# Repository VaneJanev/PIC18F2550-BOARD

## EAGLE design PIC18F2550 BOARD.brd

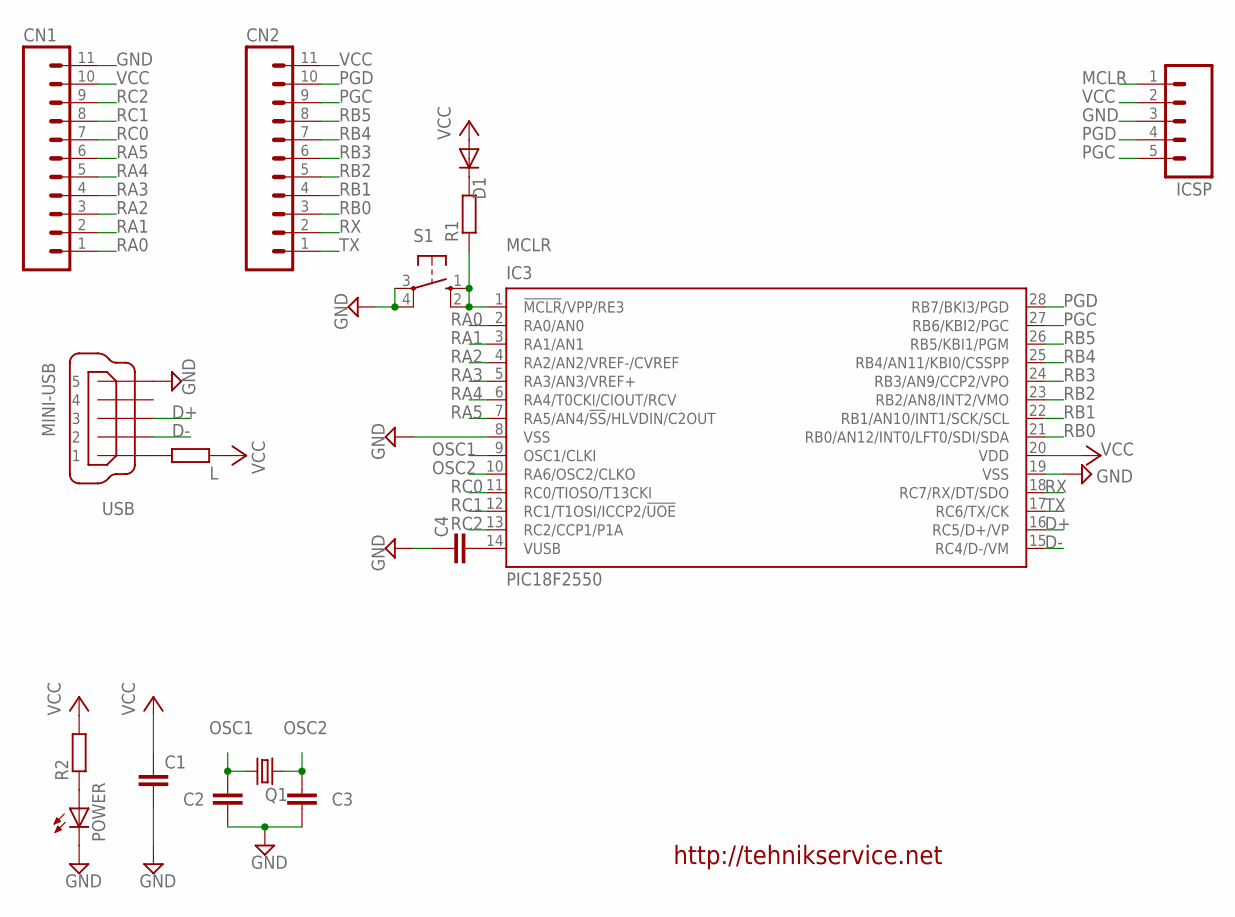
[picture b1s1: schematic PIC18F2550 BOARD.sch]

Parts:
C1, C2, C3, C4: C-EUC0402; C0402
CN1, CN2: M11; 11P
D1: DIODE-DO214AC; DO214AC
IC3: PIC18F2550; SO28W
ICSP: M05; 05P
L: R-EU_R0402; R0402
POWER: LEDCHIP-LED0805; CHIP-LED0805
Q1: CRYSTALHC49S; HC49/S
R1, R2: R-EU_R0402; R0402
S1: 10-XX; B3F-10XX
USB: MINI-USB; 32005-201

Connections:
D+: IC3.16 (RC5/D+/VP), USB.3
D-: IC3.15 (RC4/D-/VM), USB.2
GND: C1.2, C2.2, C3.2, C4.1, CN1.11, IC3.8 (VSS), IC3.19 (VSS), ICSP.3, POWER.C, S1.3, S1.4 (P1), USB.5
MCLR: IC3.1 (!MCLR!/VPP/RE3), ICSP.1, R1.1, S1.1 (S), S1.2 (S1)
unnamed: D1.C, R1.2
unnamed: POWER.A, R2.1
unnamed: C4.2, IC3.14 (VUSB)
unnamed: L.2, USB.1
OSC1: C2.1, IC3.9 (OSC1/CLKI), Q1.1
OSC2: C3.1, IC3.10 (RA6/OSC2/CLKO), Q1.2
PGC: CN2.9, IC3.27 (RB6/KBI2/PGC), ICSP.5
PGD: CN2.10, IC3.28 (RB7/BKI3/PGD), ICSP.4
RA0: CN1.1, IC3.2 (RA0/AN0)
RA1: CN1.2, IC3.3 (RA1/AN1)
RA2: CN1.3, IC3.4 (RA2/AN2/VREF-/CVREF)
RA3: CN1.4, IC3.5 (RA3/AN3/VREF+)
RA4: CN1.5, IC3.6 (RA4/T0CKI/CIOUT/RCV)
RA5: CN1.6, IC3.7 (RA5/AN4/!SS!/HLVDIN/C2OUT)
RB0: CN2.3, IC3.21 (RB0/AN12/INT0/LFT0/SDI/SDA)
RB1: CN2.4, IC3.22 (RB1/AN10/INT1/SCK/SCL)
RB2: CN2.5, IC3.23 (RB2/AN8/INT2/VMO)
RB3: CN2.6, IC3.24 (RB3/AN9/CCP2/VPO)
RB4: CN2.7, IC3.25 (RB4/AN11/KBI0/CSSPP)
RB5: CN2.8, IC3.26 (RB5/KBI1/PGM)
RC0: CN1.7, IC3.11 (RC0/TIOSO/T13CKI)
RC1: CN1.8, IC3.12 (RC1/T1OSI/ICCP2/!UOE)
RC2: CN1.9, IC3.13 (RC2/CCP1/P1A)
RX: CN2.2, IC3.18 (RC7/RX/DT/SDO)
TX: CN2.1, IC3.17 (RC6/TX/CK)
VCC: C1.1, CN1.10, CN2.11, D1.A, IC3.20 (VDD), ICSP.2, L.1, R2.2

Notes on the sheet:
http://tehnikservice.net

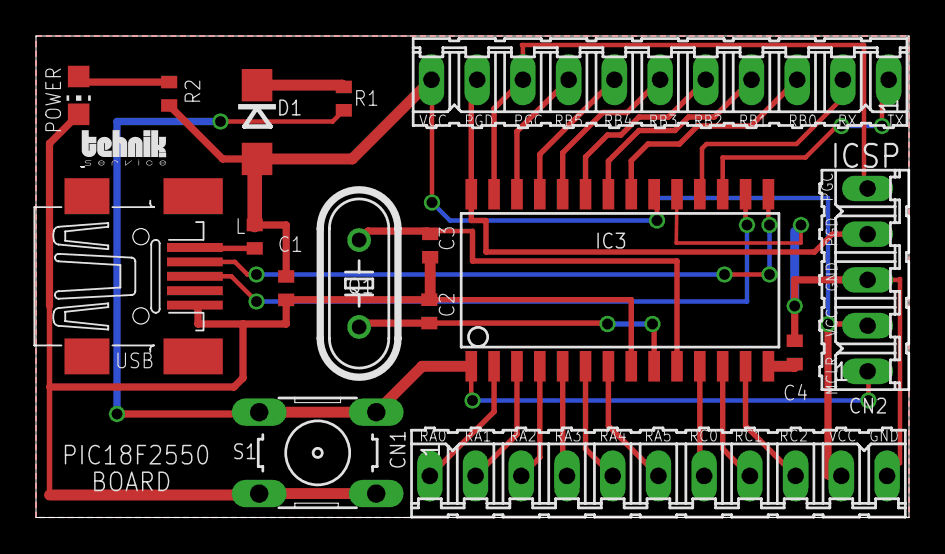
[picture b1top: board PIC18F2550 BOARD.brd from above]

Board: 2 copper layers, 48.5 x 26.8 mm, 17 parts (0 on the bottom side), 30 nets.

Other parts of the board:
U$1: LOGOT

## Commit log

2015-06-03 :tada: Added .gitattributes
2015-06-03 PIC18F2550 BOARD
    Eagle Design
